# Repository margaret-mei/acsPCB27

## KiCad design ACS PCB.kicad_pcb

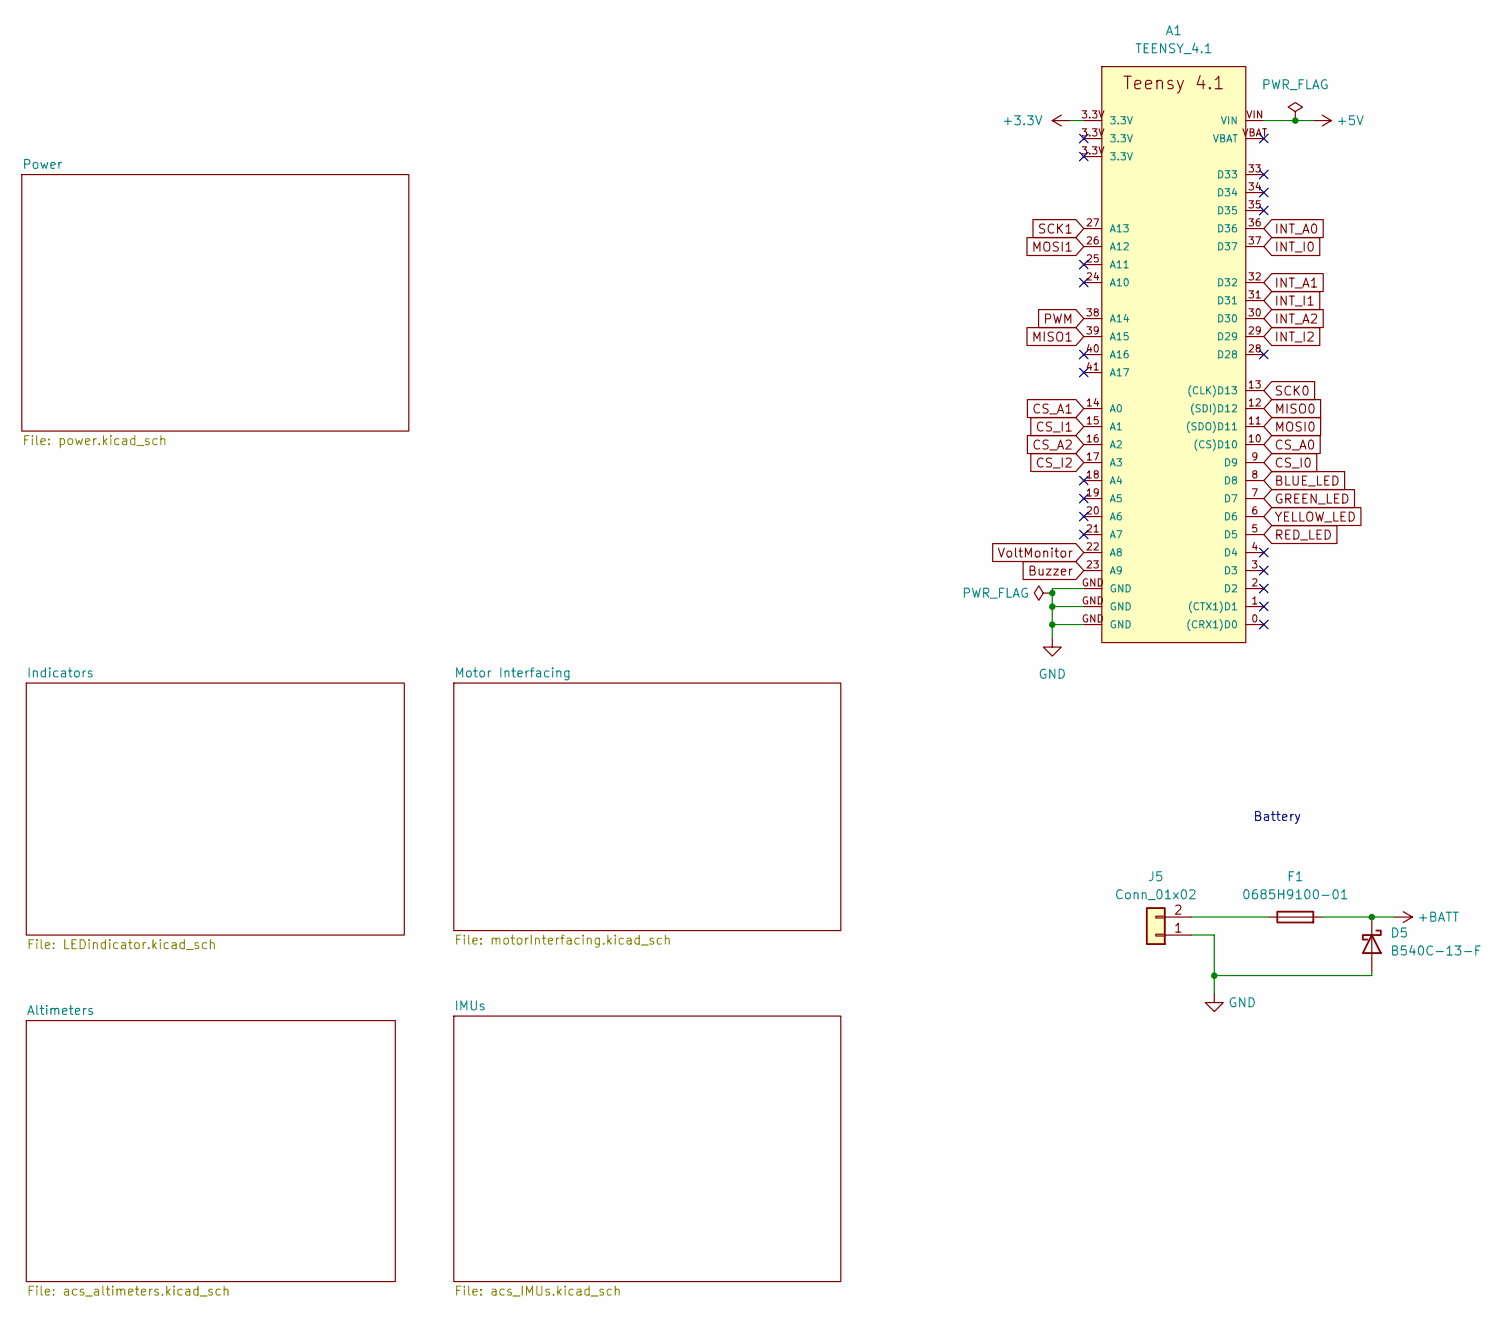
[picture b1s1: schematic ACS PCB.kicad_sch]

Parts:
A1: TEENSY_4.1; Teensy41
D5: B540C-13-F; D_SMC
F1: 0685H9100-01; Fuse_1206_3216Metric
J5: Conn_01x02; AMASS_XT60-F_1x02_P7.20mm_Vertical

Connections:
+3.3V: A1.3.3V; also elsewhere on the board
+5V: A1.VIN; also elsewhere on the board
+BATT: D5.1 (K), F1.2; also elsewhere on the board
BLUE_LED: A1.8 (D8); also elsewhere on the board
Buzzer: A1.23 (A9); also elsewhere on the board
CS_A0: A1.10 ((CS)D10); also elsewhere on the board
CS_A1: A1.14 (A0); also elsewhere on the board
CS_A2: A1.16 (A2); also elsewhere on the board
CS_I0: A1.9 (D9); also elsewhere on the board
CS_I1: A1.15 (A1); also elsewhere on the board
CS_I2: A1.17 (A3); also elsewhere on the board
GND: A1.GND, D5.2 (A), J5.1; also elsewhere on the board
GREEN_LED: A1.7 (D7); also elsewhere on the board
INT_A0: A1.36 (D36); also elsewhere on the board
INT_A1: A1.32 (D32); also elsewhere on the board
INT_A2: A1.30 (D30); also elsewhere on the board
INT_I0: A1.37 (D37); also elsewhere on the board
INT_I1: A1.31 (D31); also elsewhere on the board
INT_I2: A1.29 (D29); also elsewhere on the board
MISO0: A1.12 ((SDI)D12); also elsewhere on the board
MISO1: A1.39 (A15); also elsewhere on the board
MOSI0: A1.11 ((SDO)D11); also elsewhere on the board
MOSI1: A1.26 (A12); also elsewhere on the board
unnamed: F1.1, J5.2
PWM: A1.38 (A14); also elsewhere on the board
RED_LED: A1.5 (D5); also elsewhere on the board
SCK0: A1.13 ((CLK)D13); also elsewhere on the board
SCK1: A1.27 (A13); also elsewhere on the board
VoltMonitor: A1.22 (A8); also elsewhere on the board
YELLOW_LED: A1.6 (D6); also elsewhere on the board

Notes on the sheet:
Battery

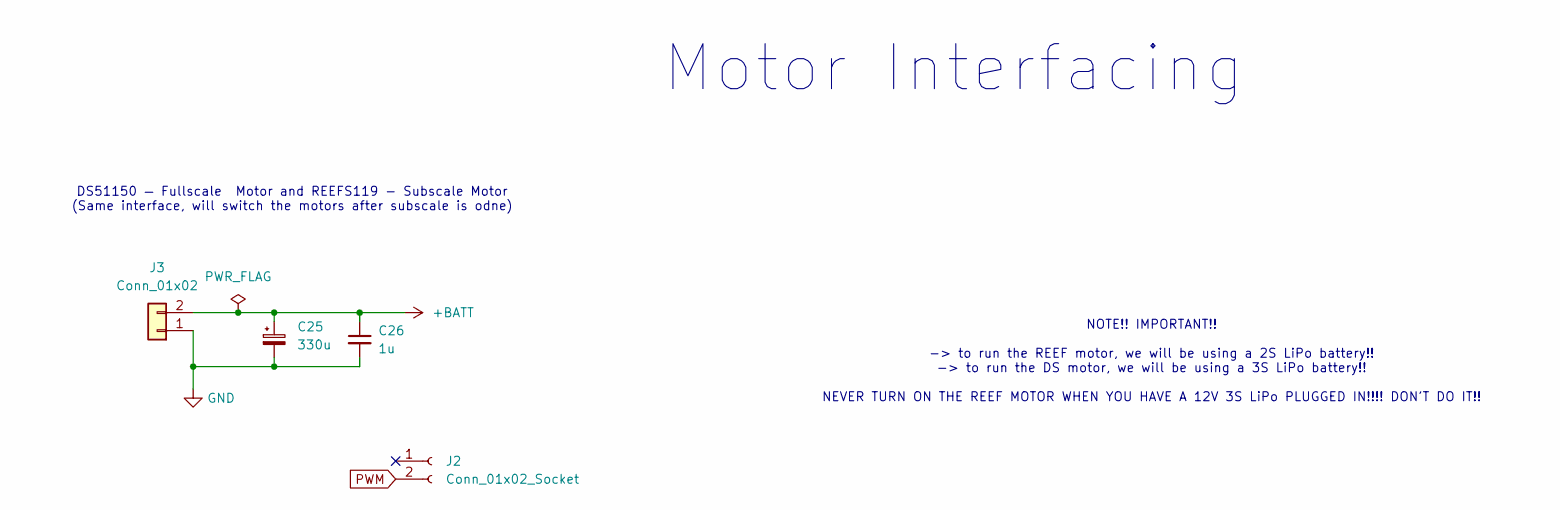
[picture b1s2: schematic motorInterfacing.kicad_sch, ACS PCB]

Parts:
C25: 330u; CP_Elec_6.3x9.9
C26: 1u; C_0805_2012Metric
J2: Conn_01x02_Socket; JST_VH_B2P-VH-B_1x02_P3.96mm_Vertical
J3: Conn_01x02; AMASS_XT30U-F_1x02_P5.0mm_Vertical

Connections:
+BATT: C25.1, C26.1, J3.2; also elsewhere on the board
GND: C25.2, C26.2, J3.1; also elsewhere on the board
PWM: J2.2 (Pin_2_2); also elsewhere on the board

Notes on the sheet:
DS51150 — Fullscale Motor and REEFS119 - Subscale Motor (Same interface, will switch the motors after subscale is odne)
Motor Interfacing
NOTE!! IMPORTANT!! -> to run the REEF motor, we will be using a 2S LiPo battery!! -> to run the DS motor, we will be using a 3S LiPo battery!! NEVER TURN ON THE REEF MOTOR WHEN YOU HAVE A 12V 3S LiPo PLUGGED IN!!!! DON'T DO IT!!

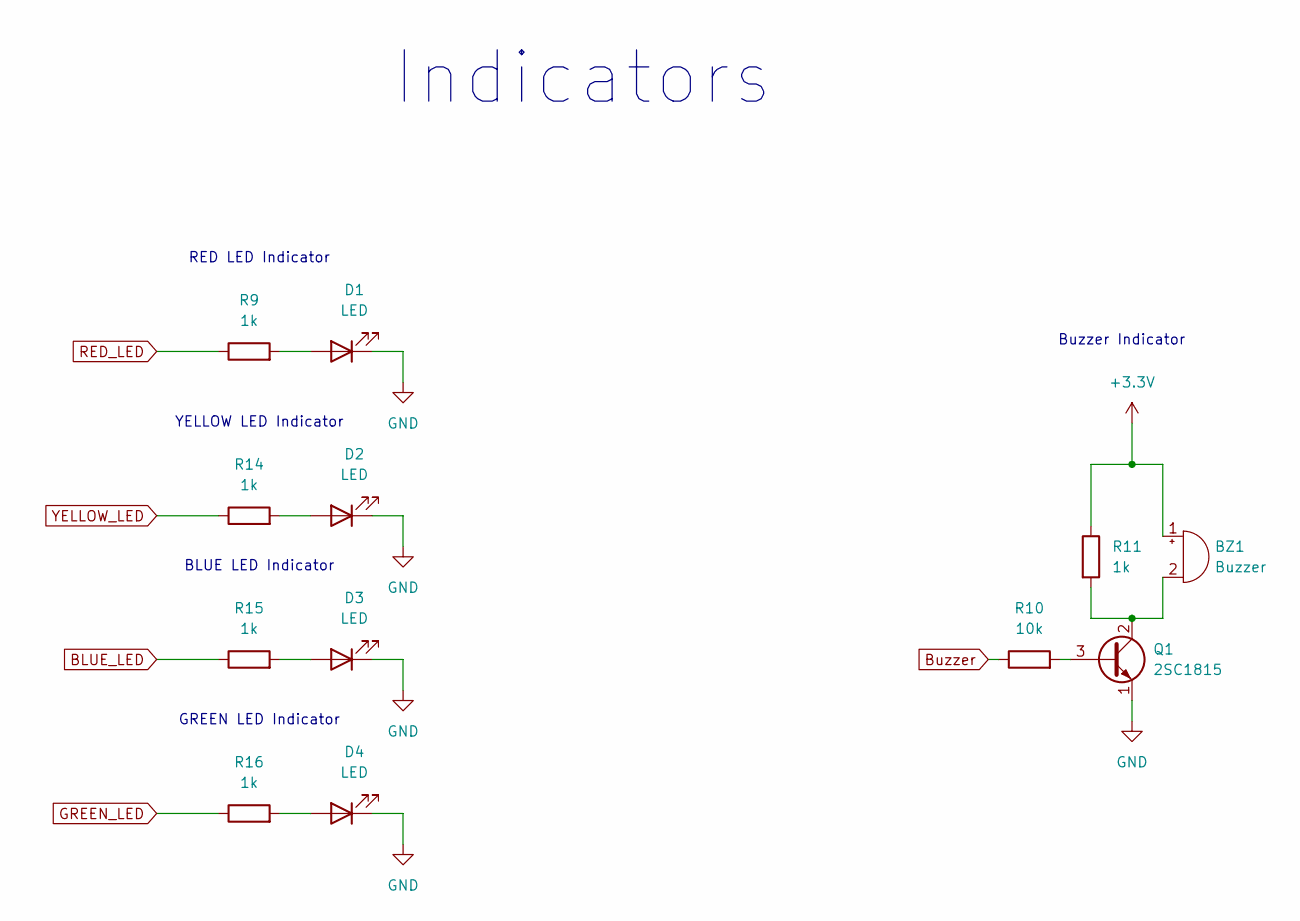
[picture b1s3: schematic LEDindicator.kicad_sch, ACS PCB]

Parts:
BZ1: Buzzer; Buzzer_TDK_PS1240P02BT_D12.2mm_H6.5mm
D1, D2, D3, D4: LED; LED_0805_2012Metric
Q1: 2SC1815; TO-92_Inline
R9, R11, R14, R15, R16: 1k; R_0805_2012Metric
R10: 10k; R_0805_2012Metric

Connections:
+3.3V: BZ1.1 (+), R11.1; also elsewhere on the board
BLUE_LED: R15.1; also elsewhere on the board
Buzzer: R10.1; also elsewhere on the board
GND: D1.1 (K), D2.1 (K), D3.1 (K), D4.1 (K), Q1.1 (E); also elsewhere on the board
GREEN_LED: R16.1; also elsewhere on the board
unnamed: BZ1.2 (-), Q1.2 (C), R11.2
unnamed: D1.2 (A), R9.2
unnamed: D2.2 (A), R14.2
unnamed: D3.2 (A), R15.2
unnamed: D4.2 (A), R16.2
unnamed: Q1.3 (B), R10.2
RED_LED: R9.1; also elsewhere on the board
YELLOW_LED: R14.1; also elsewhere on the board

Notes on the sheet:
BLUE LED Indicator
Buzzer Indicator
Indicators
RED LED Indicator
YELLOW LED Indicator
GREEN LED Indicator

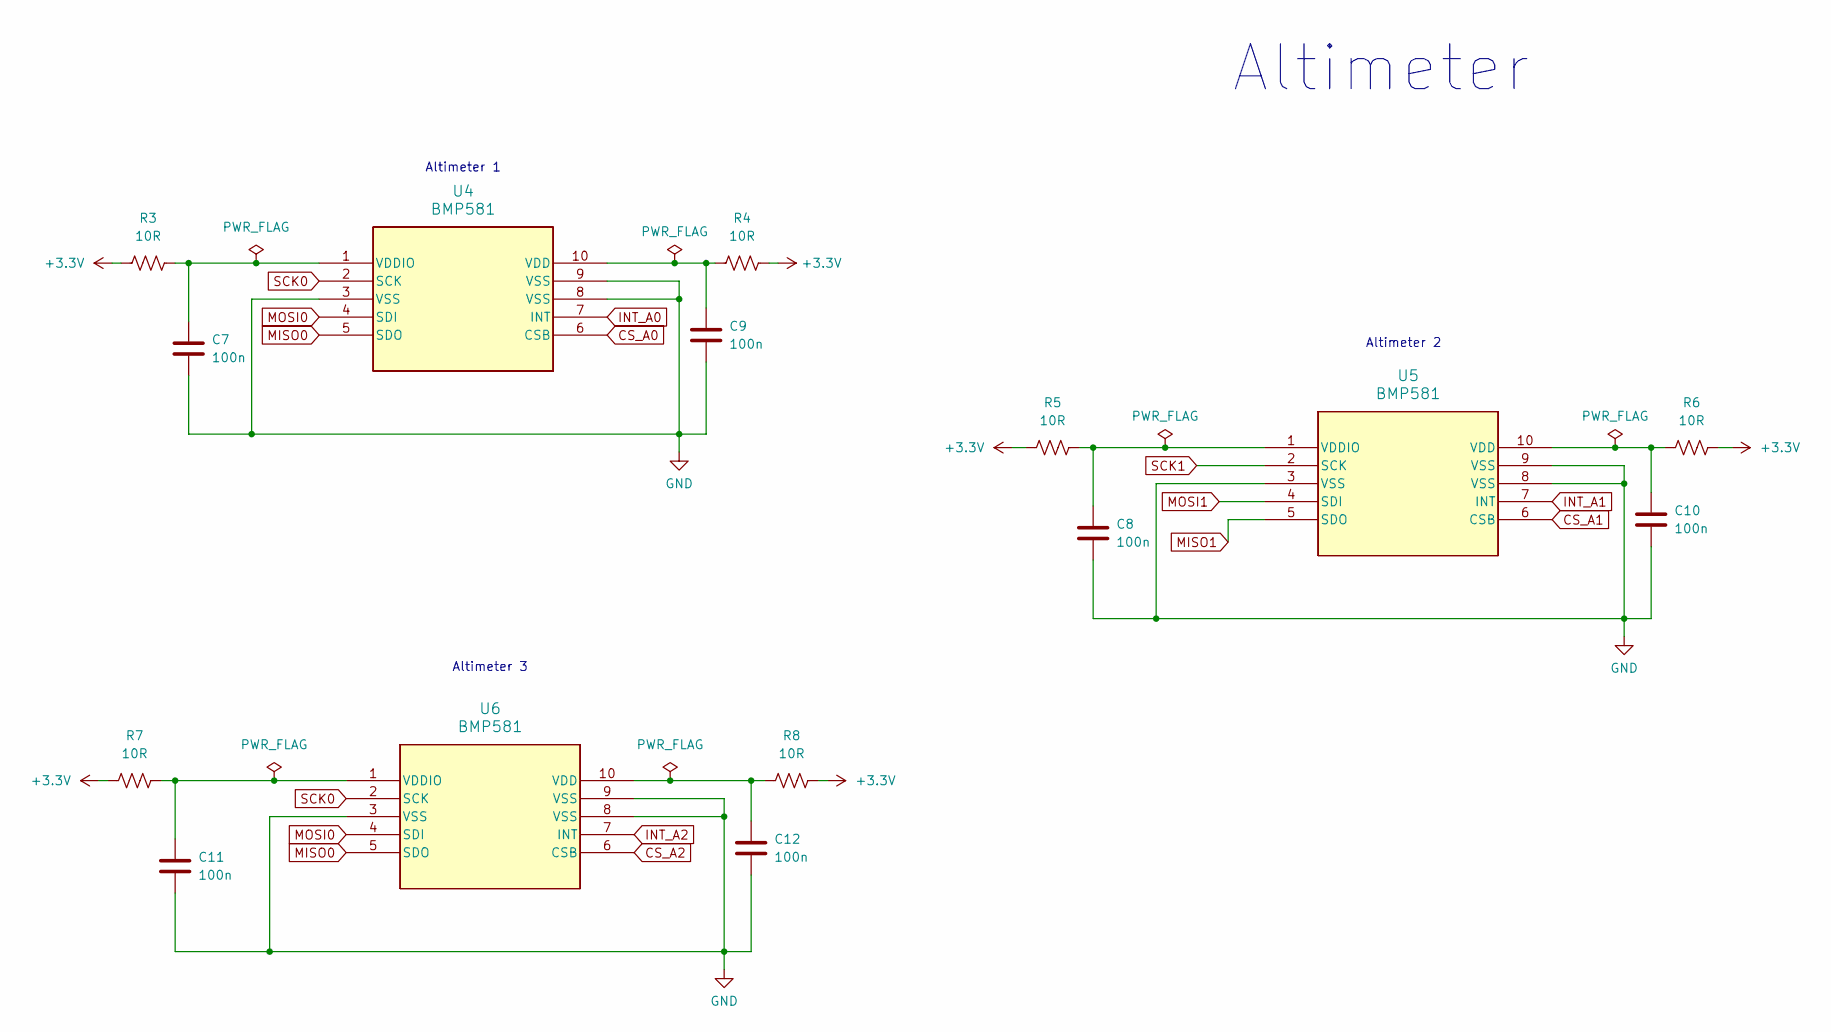
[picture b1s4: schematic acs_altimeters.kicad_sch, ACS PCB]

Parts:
C7, C8, C9, C10, C11, C12: 100n; C_0603_1608Metric
R3, R4, R5, R6, R7, R8: 10R; R_0603_1608Metric
U4, U5, U6: BMP581; QFN10_BMP581_BOS

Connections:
+3.3V: R3.2, R4.2, R5.2, R6.2, R7.2, R8.2; also elsewhere on the board
CS_A0: U4.6 (CSB); also elsewhere on the board
CS_A1: U5.6 (CSB); also elsewhere on the board
CS_A2: U6.6 (CSB); also elsewhere on the board
GND: C7.2, C8.2, C9.1, C10.1, C11.2, C12.1, U4.3 (VSS), U4.8 (VSS), U4.9 (VSS), U5.3 (VSS), U5.8 (VSS), U5.9 (VSS), U6.3 (VSS), U6.8 (VSS), U6.9 (VSS); also elsewhere on the board
INT_A0: U4.7 (INT); also elsewhere on the board
INT_A1: U5.7 (INT); also elsewhere on the board
INT_A2: U6.7 (INT); also elsewhere on the board
MISO0: U4.5 (SDO), U6.5 (SDO); also elsewhere on the board
MISO1: U5.5 (SDO); also elsewhere on the board
MOSI0: U4.4 (SDI), U6.4 (SDI); also elsewhere on the board
MOSI1: U5.4 (SDI); also elsewhere on the board
unnamed: C9.2, R4.1, U4.10 (VDD)
unnamed: C7.1, R3.1, U4.1 (VDDIO)
unnamed: C10.2, R6.1, U5.10 (VDD)
unnamed: C8.1, R5.1, U5.1 (VDDIO)
unnamed: C12.2, R8.1, U6.10 (VDD)
unnamed: C11.1, R7.1, U6.1 (VDDIO)
SCK0: U4.2 (SCK), U6.2 (SCK); also elsewhere on the board
SCK1: U5.2 (SCK); also elsewhere on the board

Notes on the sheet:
Altimeter 1
Altimeter 3
Altimeter
Altimeter 2

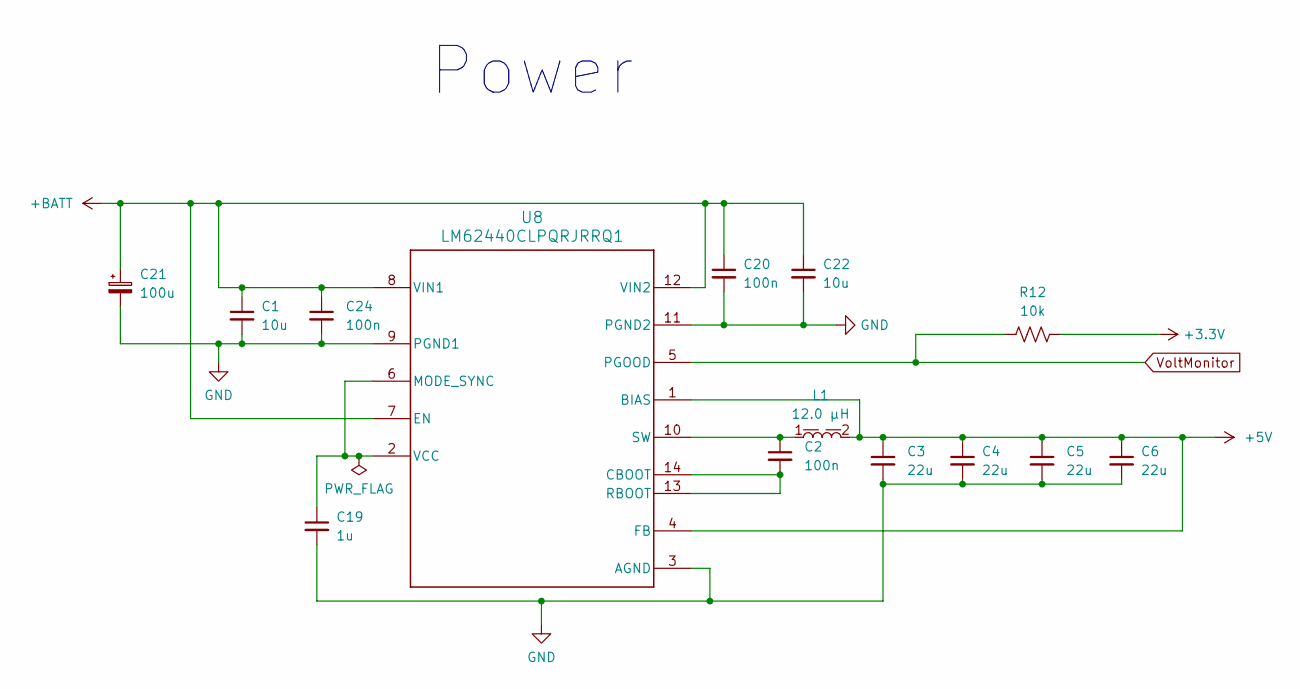
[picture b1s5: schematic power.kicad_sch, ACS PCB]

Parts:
C1, C22: 10u; C_0805_2012Metric
C2, C20, C24: 100n; C_0603_1608Metric
C3, C4, C5, C6: 22u; C_1206_3216Metric
C19: 1u; C_0603_1608Metric
C21: 100u; CP_Elec_8x6.7
L1: 5030_7443845030120; wurst7443845030120; Part Number 7443845030120
R12: 10k; R_0603_1608Metric
U8: LM62440CLPQRJRRQ1; RJR0014A-MFG

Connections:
+3.3V: R12.2; also elsewhere on the board
+5V: C3.1, C4.1, C5.1, C6.1, L1.2, U8.1 (BIAS), U8.4 (FB); also elsewhere on the board
+BATT: C1.1, C20.1, C21.1, C22.1, C24.1, U8.7 (EN), U8.8 (VIN1), U8.12 (VIN2); also elsewhere on the board
GND: C1.2, C3.2, C4.2, C5.2, C6.2, C19.2, C20.2, C21.2, C22.2, C24.2, U8.3 (AGND), U8.9 (PGND1), U8.11 (PGND2); also elsewhere on the board
unnamed: C2.2, U8.13 (RBOOT), U8.14 (CBOOT)
unnamed: C19.1, U8.2 (VCC), U8.6 (MODE_SYNC)
unnamed: C2.1, L1.1, U8.10 (SW)
VoltMonitor: R12.1, U8.5 (PGOOD); also elsewhere on the board

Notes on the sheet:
Power

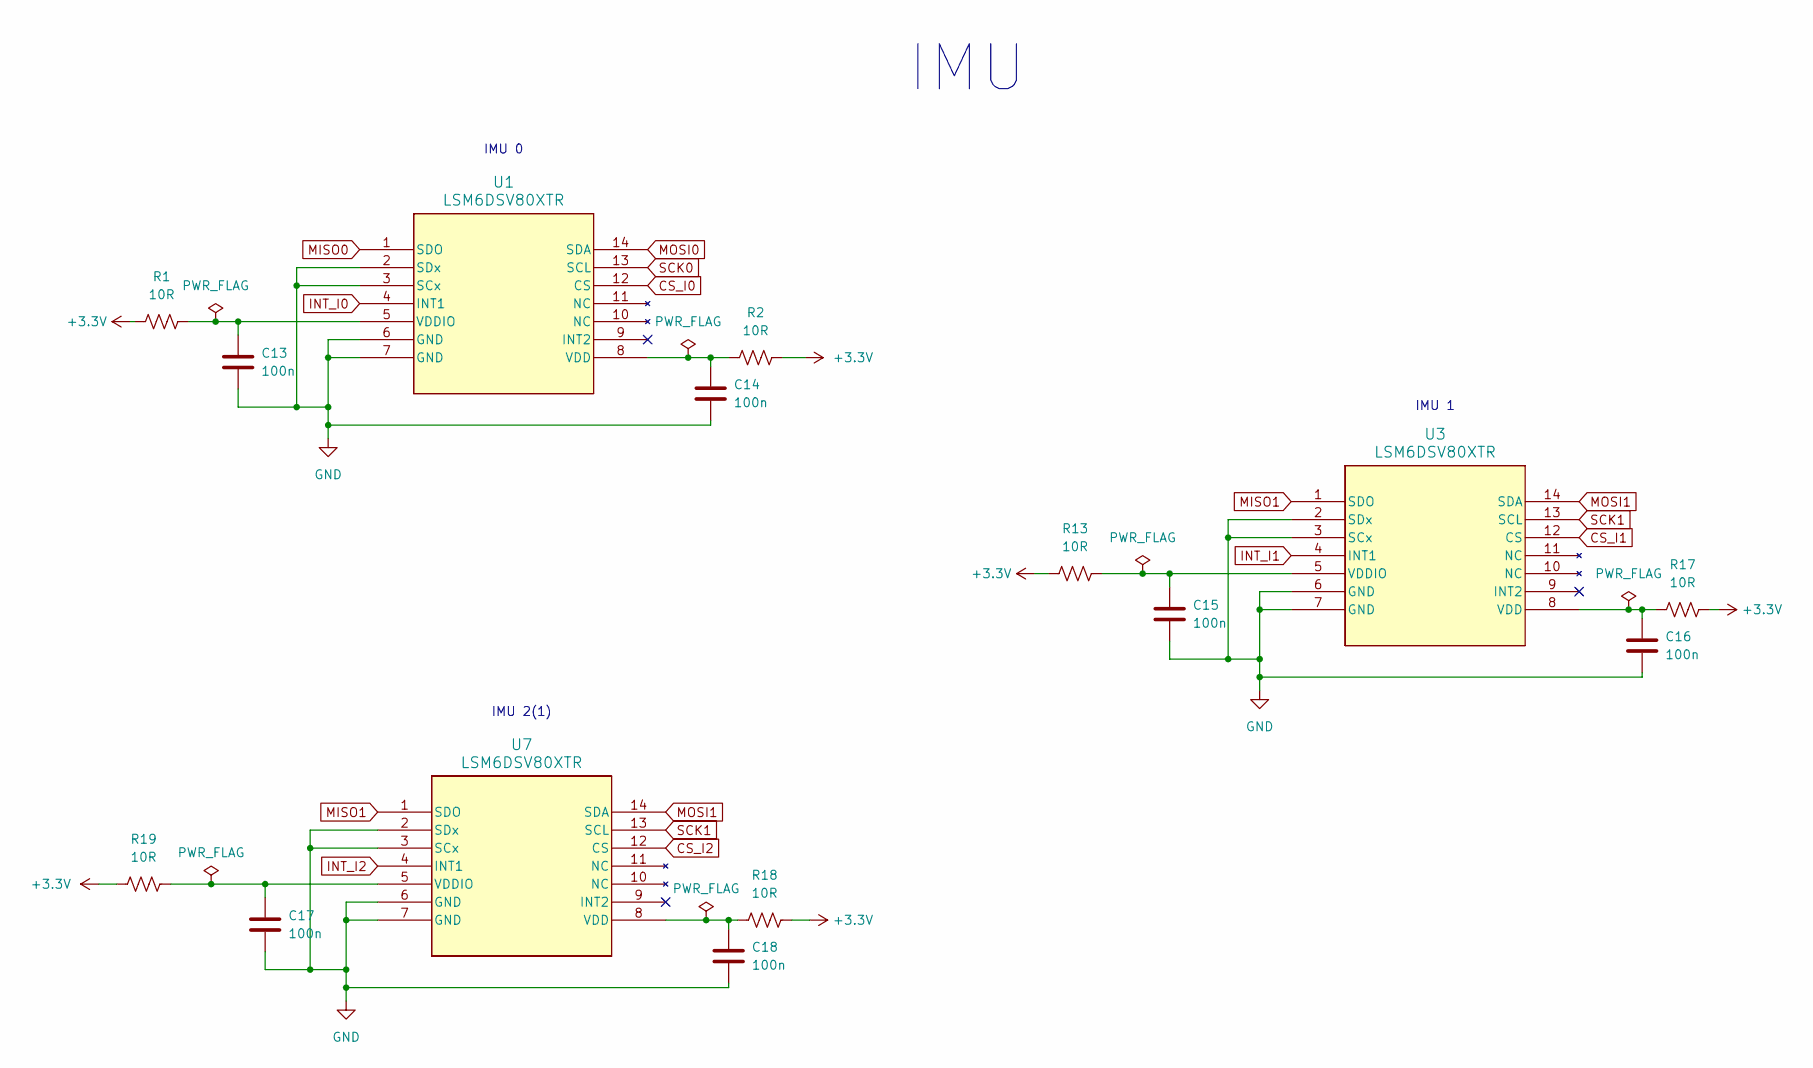
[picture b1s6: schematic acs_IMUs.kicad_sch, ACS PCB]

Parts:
C13, C14, C15, C16, C17, C18: 100n; C_0603_1608Metric
R1, R2, R13, R17, R18, R19: 10R; R_0603_1608Metric
U1, U3, U7: LSM6DSV80XTR; QFN_LSM6DSV80XTR_STM

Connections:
+3.3V: R1.1, R2.2, R13.1, R17.2, R18.2, R19.1; also elsewhere on the board
CS_I0: U1.12 (CS); also elsewhere on the board
CS_I1: U3.12 (CS); also elsewhere on the board
CS_I2: U7.12 (CS); also elsewhere on the board
GND: C13.2, C14.2, C15.2, C16.2, C17.2, C18.2, U1.2 (SDx), U1.3 (SCx), U1.6 (GND), U1.7 (GND), U3.2 (SDx), U3.3 (SCx), U3.6 (GND), U3.7 (GND), U7.2 (SDx), U7.3 (SCx), U7.6 (GND), U7.7 (GND); also elsewhere on the board
INT_I0: U1.4 (INT1); also elsewhere on the board
INT_I1: U3.4 (INT1); also elsewhere on the board
INT_I2: U7.4 (INT1); also elsewhere on the board
MISO0: U1.1 (SDO); also elsewhere on the board
MISO1: U3.1 (SDO), U7.1 (SDO); also elsewhere on the board
MOSI0: U1.14 (SDA); also elsewhere on the board
MOSI1: U3.14 (SDA), U7.14 (SDA); also elsewhere on the board
unnamed: C14.1, R2.1, U1.8 (VDD)
unnamed: C13.1, R1.2, U1.5 (VDDIO)
unnamed: C16.1, R17.1, U3.8 (VDD)
unnamed: C15.1, R13.2, U3.5 (VDDIO)
unnamed: C18.1, R18.1, U7.8 (VDD)
unnamed: C17.1, R19.2, U7.5 (VDDIO)
SCK0: U1.13 (SCL); also elsewhere on the board
SCK1: U3.13 (SCL), U7.13 (SCL); also elsewhere on the board

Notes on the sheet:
IMU 2(1)
IMU 0
IMU 1
IMU

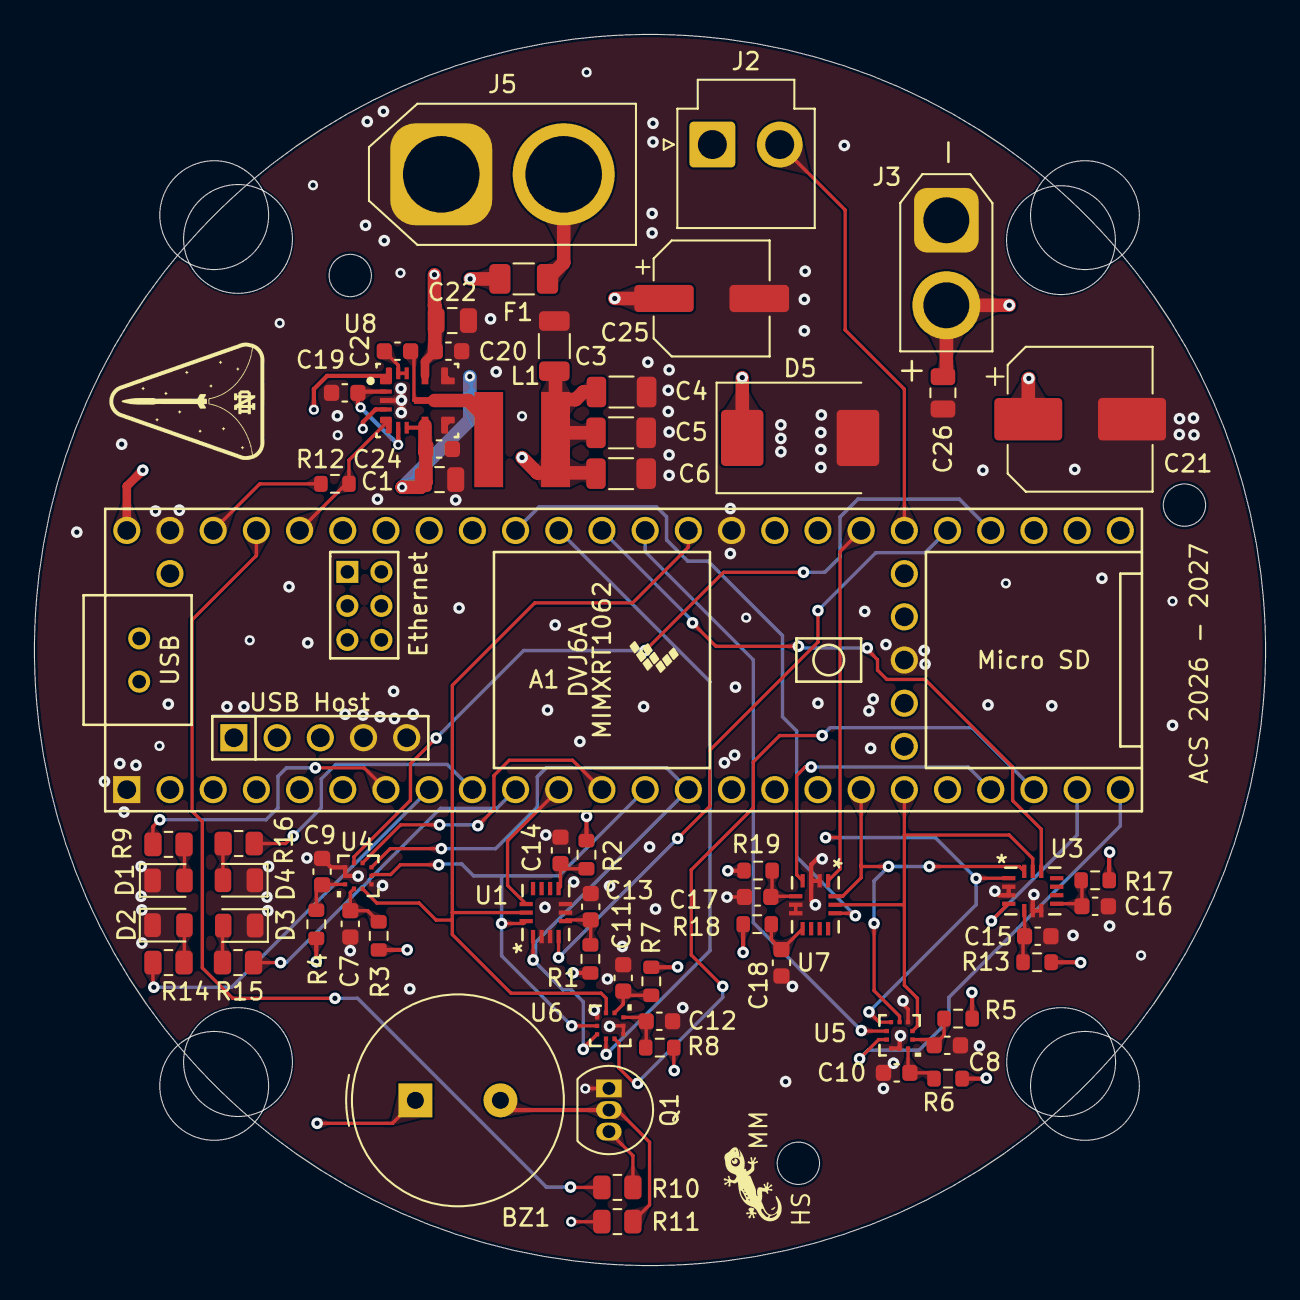
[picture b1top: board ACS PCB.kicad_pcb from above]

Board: 4 copper layers, 72.4 x 72.4 mm, 64 parts (0 on the bottom side), 51 nets.

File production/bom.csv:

Designator,Footprint,Quantity,Value,LCSC Part #
"_8, _7, _6, _5, _4, _3, _2, ",,8,,
A1,Teensy41,1,TEENSY_4.1,
BZ1,Buzzer_TDK_PS1240P02BT_D12.2mm_H6.5mm,1,Buzzer,
"C1, C22",0805,2,10u,
"C10, C11, C12, C13, C14, C15, C16, C17, C18, C2, C20, C24, C7, C8, C9",0603,15,100n,
C19,0603,1,1u,
C21,CP_Elec_8x6.7,1,100u,
C25,CP_Elec_6.3x9.9,1,330u,
C26,0805,1,1u,
"C3, C4, C5, C6",1206,4,22u,
"D1, D2, D3, D4",0805,4,LED,
D5,D_SMC,1,B540C-13-F,
F1,1206,1,0685H9100-01,
J2,JST_VH_B2P-VH-B_1x02_P3.96mm_Vertical,1,Conn_01x02_Socket,
J3,AMASS_XT30U-F_1x02_P5.0mm_Vertical,1,Conn_01x02,
J5,AMASS_XT60-F_1x02_P7.20mm_Vertical,1,Conn_01x02,
L1,wurst7443845030120,1,5030_7443845030120,
Q1,TO-92_Inline,1,2SC1815,
"R1, R13, R17, R18, R19, R2, R3, R4, R5, R6, R7, R8",0603,12,10R,
R10,0805,1,10k,
"R11, R14, R15, R16, R9",0805,5,1k,
R12,0603,1,10k,
"U1, U3, U7",QFN_LSM6DSV80XTR_STM,3,LSM6DSV80XTR,
"U4, U5, U6",QFN10_BMP581_BOS,3,BMP581,
U8,RJR0014A-MFG,1,LM62440CLPQRJRRQ1,
